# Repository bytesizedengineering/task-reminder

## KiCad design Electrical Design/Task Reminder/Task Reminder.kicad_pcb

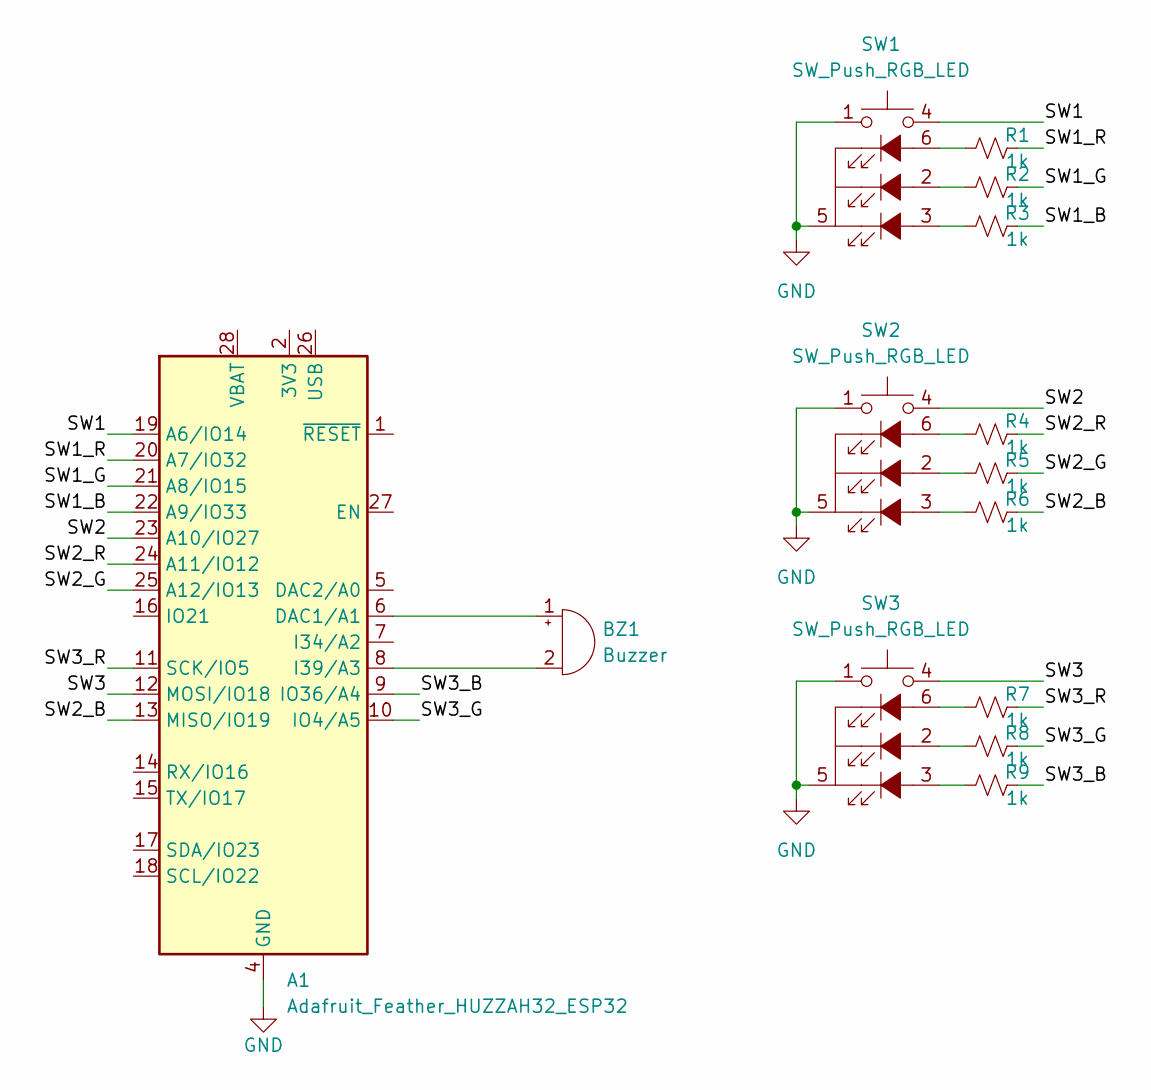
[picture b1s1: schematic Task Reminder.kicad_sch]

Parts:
A1: Adafruit_Feather_HUZZAH32_ESP32; Adafruit_Feather
BZ1: Buzzer; Buzzer_Murata_PKMCS0909E
R1, R2, R3, R4, R5, R6, R7, R8, R9: 1k; R_0805_2012Metric
SW1, SW2, SW3: SW_Push_RGB_LED; Push_BH16NBBBRGB

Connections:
/SW1: A1.19 (A6/IO14), SW1.4
/SW1_B: A1.22 (A9/IO33), R3.2
/SW1_G: A1.21 (A8/IO15), R2.2
/SW1_R: A1.20 (A7/IO32), R1.2
/SW2: A1.23 (A10/IO27), SW2.4
/SW2_B: A1.13 (MISO/IO19), R6.2
/SW2_G: A1.25 (A12/IO13), R5.2
/SW2_R: A1.24 (A11/IO12), R4.2
/SW3: A1.12 (MOSI/IO18), SW3.4
/SW3_B: A1.9 (IO36/A4), R9.2
/SW3_G: A1.10 (IO4/A5), R8.2
/SW3_R: A1.11 (SCK/IO5), R7.2
GND: A1.4 (GND), SW1.1, SW1.5 (C), SW2.1, SW2.5 (C), SW3.1, SW3.5 (C)
unnamed: A1.6 (DAC1/A1), BZ1.1 (-)
unnamed: A1.8 (I39/A3), BZ1.2 (+)
unnamed: R3.1, SW1.3 (B)
unnamed: R2.1, SW1.2 (G)
unnamed: R1.1, SW1.6 (R)
unnamed: R6.1, SW2.3 (B)
unnamed: R5.1, SW2.2 (G)
unnamed: R4.1, SW2.6 (R)
unnamed: R9.1, SW3.3 (B)
unnamed: R8.1, SW3.2 (G)
unnamed: R7.1, SW3.6 (R)

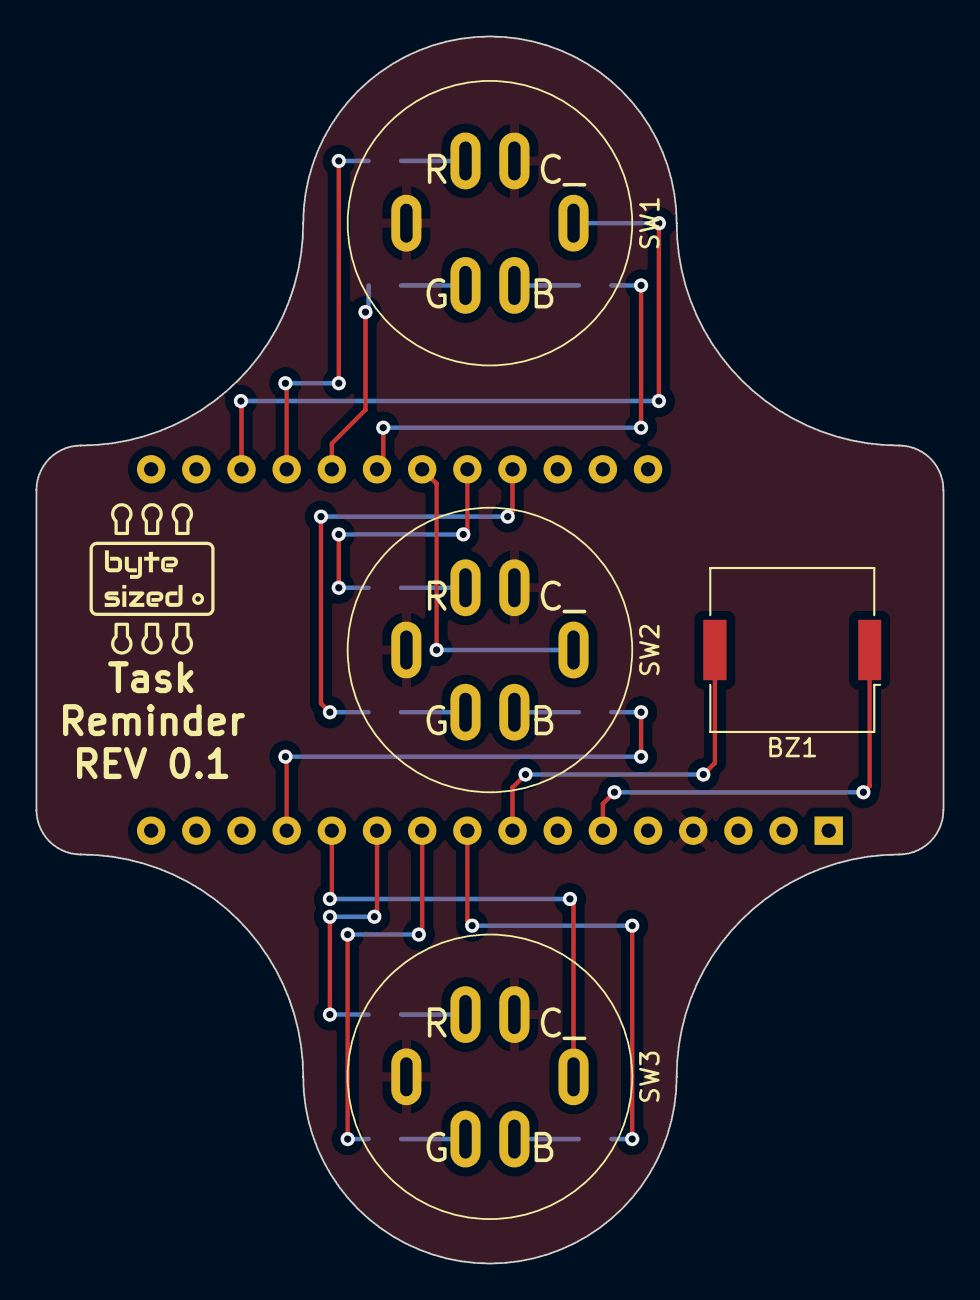
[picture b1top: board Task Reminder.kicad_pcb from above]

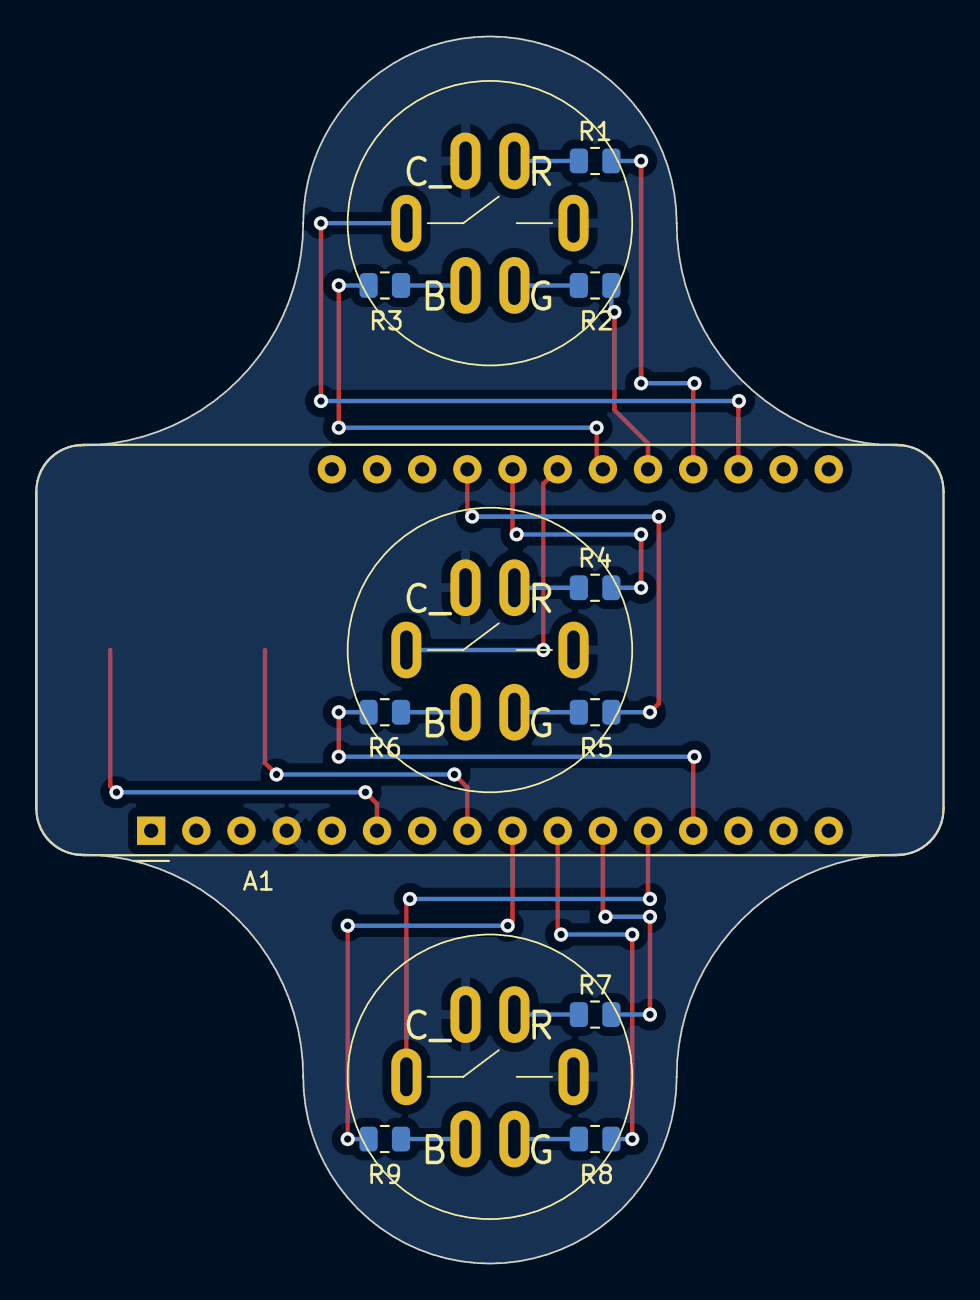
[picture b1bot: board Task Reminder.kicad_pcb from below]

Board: 2 copper layers, 51.0 x 69.0 mm, 14 parts (10 on the bottom side), 24 nets.

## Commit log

2024-03-05 changed revision
    changed revision from B to 0.1 in mechanical design file names
